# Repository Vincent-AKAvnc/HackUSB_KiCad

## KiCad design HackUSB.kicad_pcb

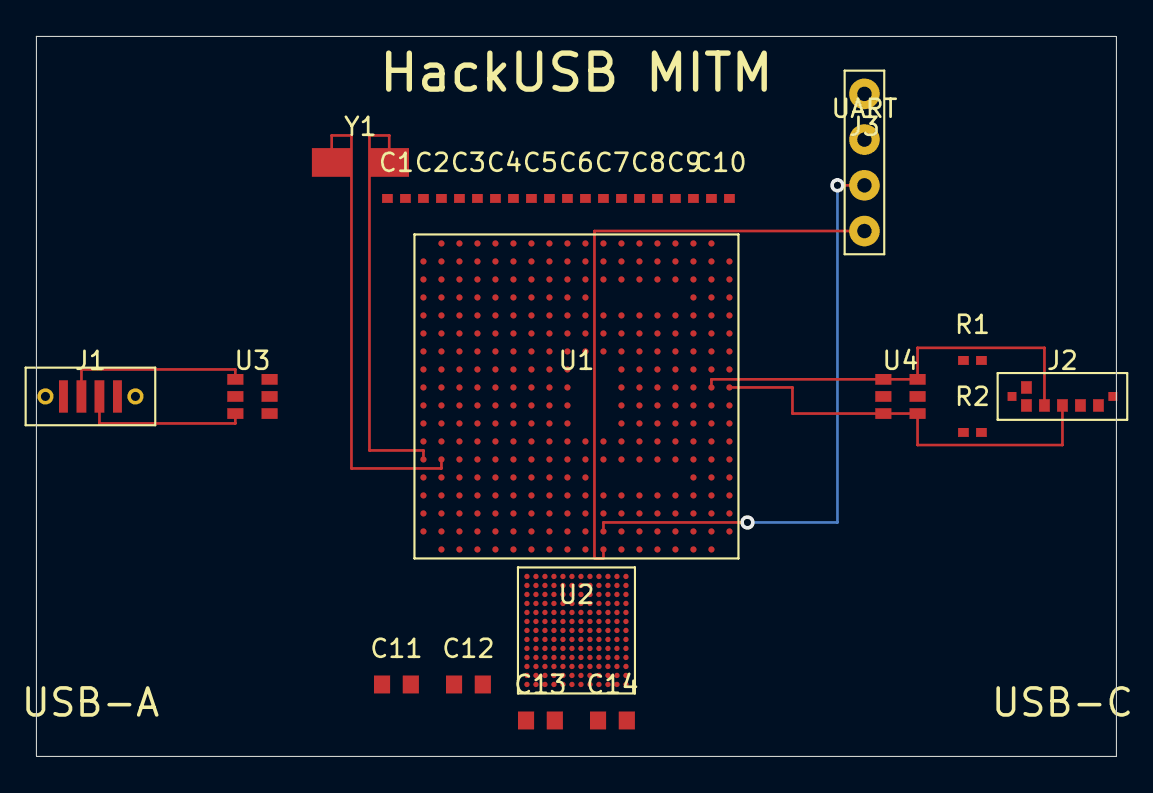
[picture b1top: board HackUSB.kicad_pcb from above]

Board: 4 copper layers, 60.0 x 40.0 mm, 24 parts (0 on the bottom side), 23 nets.

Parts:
C1, C2, C3, C4, C5, C6, C7, C8, C9, C10: 100nF; C_0402
C11, C12, C13, C14: 10uF; C_0603
J1: USB-A-Male-SMD; USB_A_Male_SMD
J2: USB-C-Male-SMD; USB_C_Male_SMD
J3: UART-Header-1x4; PinHeader_1x04_P2.54mm_Vertical
R1, R2: 5.1k; R_0402
U1: OSD32MP157F-512M-EAA; OSD32MP15X-BGA-324
U2: eMMC-BGA153
U3, U4: USBLC6-2SC6; SOT-23-6
Y1: 32.768kHz; Crystal_SMD_3215-2pin

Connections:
+3V3: C1.1, C2.1, C3.1, C4.1, C5.1, C6.1, C7.1, C8.1, C9.1, C10.1, J3.2, R1.1, R2.1, U2.A12
+5V_VBUS: C11.1, C12.1, C13.1, C14.1, J1.1, J2.1, U3.2, U4.2
CC1: J2.4, R1.2
CC2: J2.5, R2.2
GND: C1.2, C2.2, C3.2, C4.2, C5.2, C6.2, C7.2, C8.2, C9.2, C10.2, C11.2, C12.2, C13.2, C14.2, J1.4, J2.6, J3.1, U1.F9, U1.F10, U1.F11, U1.G11, U2.A3, U2.A6, U2.A9, U2.N3, U2.N6, U2.N9, U3.5, U4.5
OSC32_IN: U1.N2, Y1.1
OSC32_OUT: U1.N1, Y1.2
SDMMC1_CLK: U1.V17, U2.A1
SDMMC1_CMD: U1.U18, U2.A2
SDMMC1_D0: U1.T16, U2.B1
SDMMC1_D1: U1.U16, U2.B2
SDMMC1_D2: U1.V16, U2.B3
SDMMC1_D3: U1.U17, U2.B4
SDMMC1_D4: U1.T13, U2.B5
SDMMC1_D5: U1.U13, U2.B6
SDMMC1_D6: U1.R18, U2.B7
SDMMC1_D7: U1.R16, U2.B8
UART4_RX: J3.4, U1.V11
UART4_TX: J3.3, U1.U11
USB_A_DM: J1.2, U1.K18, U3.3, U3.4
USB_A_DP: J1.3, U1.K17, U3.1, U3.6
USB_C_DM: J2.2, U1.J17, U4.3, U4.4
USB_C_DP: J2.3, U1.J18, U4.1, U4.6

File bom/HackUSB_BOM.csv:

Reference,Value,Footprint,MPN,Fournisseur,Quantité,Description
U1,OSD32MP15x,BGA-361 11.6x11.6mm,OSD32MP1516-RED,Octavo Systems / Mouser,1,SiP STM32MP157 + STPMIC1 + LPDDR3 512MB
U2,MTFC4GACAJCN,BGA-153 7x11.5mm,MTFC4GACAJCN-4M,Micron / DigiKey,1,eMMC 4GB HS200 3.3V/1.8V
U3,USBLC6-2SC6,SOT-23-6,USBLC6-2SC6Y,STMicro / Mouser,1,ESD protection USB-A side
U4,USBLC6-2SC6,SOT-23-6,USBLC6-2SC6Y,STMicro / Mouser,1,ESD protection USB-C side
J1,USB-A Male,USB_A_Molex_67643_Horizontal,0678404001,Molex / Mouser,1,Connecteur USB-A male (côté PC)
J2,USB-C Male,USB_C_GCT_USB4135,USB4135-GF-A,GCT / DigiKey,1,Connecteur USB-C male (côté Coral TPU)
Y1,32.768kHz,Crystal_SMD_3215-2Pin,NX3215SA-32.768K-EXS00A-CS05480,NDK / DigiKey,1,Cristal RTC 32.768kHz
J3,UART4_DEBUG,PinHeader_1x04_P2.54mm,61300411121,Würth / DigiKey,1,Header UART4 debug 4 broches
C1,100nF 10V,C_0402_1005Metric,GRM155R71A104KA01D,Murata / DigiKey,1,Découplage VDD_CORE
C2,100nF 10V,C_0402_1005Metric,GRM155R71A104KA01D,Murata / DigiKey,1,Découplage VDD_3V3
C3,100nF 10V,C_0402_1005Metric,GRM155R71A104KA01D,Murata / DigiKey,1,Découplage USB OTG
C4,100nF 10V,C_0402_1005Metric,GRM155R71A104KA01D,Murata / DigiKey,1,Découplage USB HOST
C5,100nF 10V,C_0402_1005Metric,GRM155R71A104KA01D,Murata / DigiKey,1,Découplage SDMMC1
C6,100nF 10V,C_0402_1005Metric,GRM155R71A104KA01D,Murata / DigiKey,1,Découplage SDMMC1
C7,100nF 10V,C_0402_1005Metric,GRM155R71A104KA01D,Murata / DigiKey,1,Découplage général
C8,100nF 10V,C_0402_1005Metric,GRM155R71A104KA01D,Murata / DigiKey,1,Découplage général
C9,100nF 10V,C_0402_1005Metric,GRM155R71A104KA01D,Murata / DigiKey,1,Découplage UART
C10,100nF 10V,C_0402_1005Metric,GRM155R71A104KA01D,Murata / DigiKey,1,Découplage RTC
C11,10uF 10V,C_0603_1608Metric,GRM188R61A106KE69D,Murata / DigiKey,1,Bulk VIN
C12,10uF 10V,C_0603_1608Metric,GRM188R61A106KE69D,Murata / DigiKey,1,Bulk VDD_3V3
C13,10uF 10V,C_0603_1608Metric,GRM188R61A106KE69D,Murata / DigiKey,1,Bulk eMMC VCC
C14,10uF 10V,C_0603_1608Metric,GRM188R61A106KE69D,Murata / DigiKey,1,Bulk VBUS
R1,5.1k 1% 0402,R_0402_1005Metric,RC0402FR-075K1L,Yageo / DigiKey,1,CC1 pull-down UFP sink
R2,5.1k 1% 0402,R_0402_1005Metric,RC0402FR-075K1L,Yageo / DigiKey,1,CC2 pull-down UFP sink
